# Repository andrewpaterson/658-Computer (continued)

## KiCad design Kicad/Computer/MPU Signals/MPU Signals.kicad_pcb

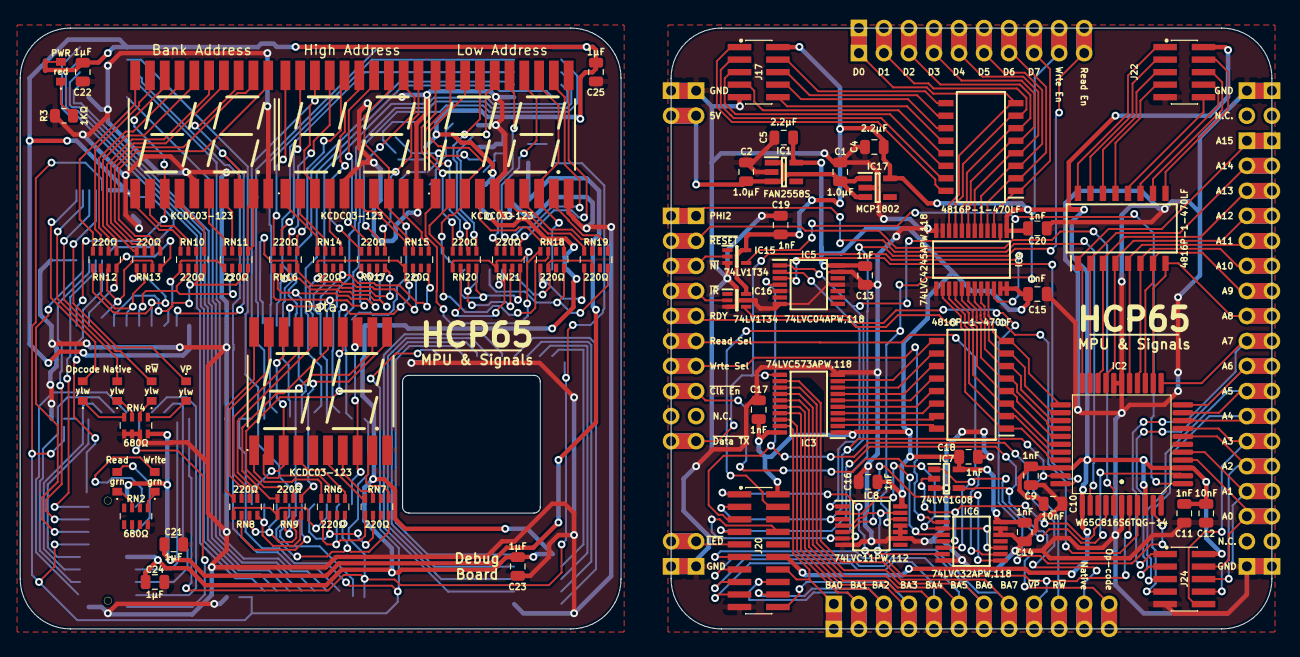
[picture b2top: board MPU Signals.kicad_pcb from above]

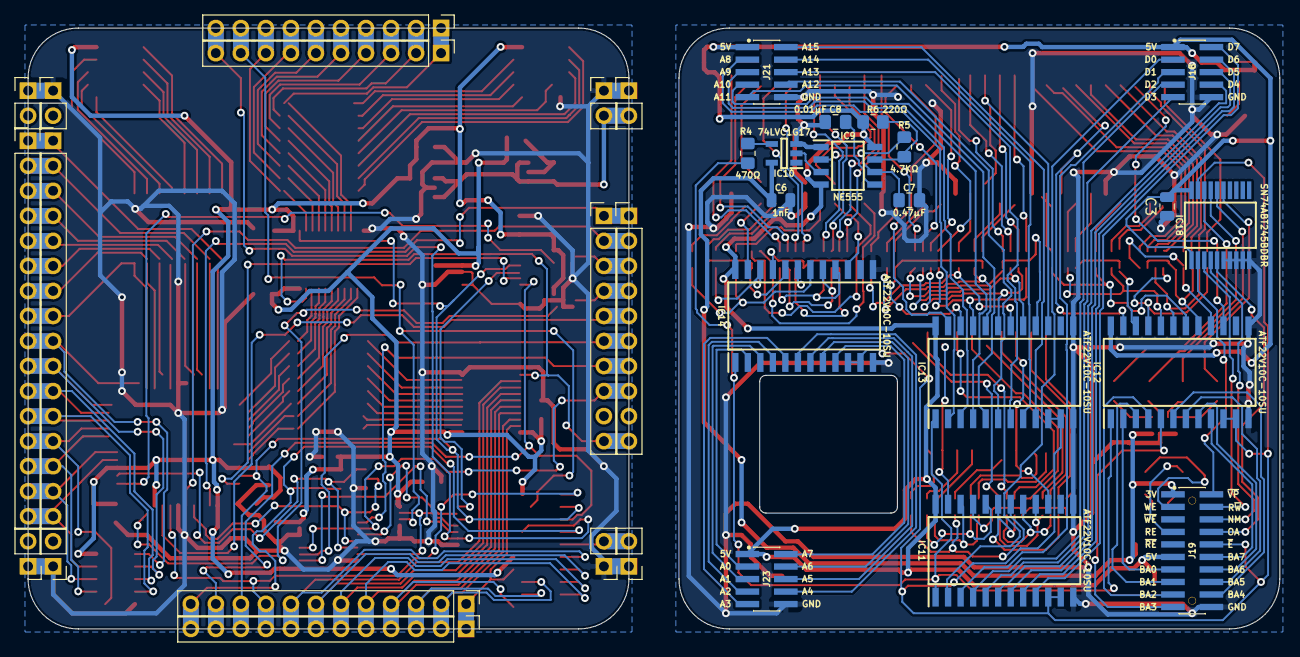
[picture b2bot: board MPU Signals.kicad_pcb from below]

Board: 2 copper layers, 127.0 x 61.0 mm, 104 parts (34 on the bottom side), 245 nets.

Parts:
C1, C2, C4, C5, C6, C9, C10, C11, C12, C13, C14, C15, C16, C17, C18, C19, C20, C21, C22, C23, C24, C25: C_0805
C3: C_Small; C_0805_2012Metric
C7, C8: C_Small; C_0805_2012Metric_Pad1.18x1.45mm_HandSolder
DS1, DS2, DS3, DS4: KCDC03-123; KCDC03123
IC1: FAN2558S38X; SOT95P270X145-5N
IC2: W65C816S6TQG-14; W65C816 PLCC 0.8mm 44 Pin
IC3: 74LVC573APW,118; SOP65P640X110-20N
IC4: 74LVC4245APW,118; SOP65P640X110-24N
IC5: 74LVC04APW,118; SOP65P640X110-14N
IC6: 74LVC32APW,118; SOP65P640X110-14N
IC7: 74LVC1G08GV,125; SOT95P275X110-5N
IC8: 74LVC11PW,112; SOP65P640X110-14N
IC9: NE555DRG4; SOIC127P600X175-8N
IC10: 74LVC1G17GV,125; SOT95P275X110-5N
IC11, IC12, IC13, IC14: ATF22V10C-10SU; SOIC127P1032X265-24N
IC15, IC16: 74LV1T34GWH; SOT65P212X110-5N
IC17: MCP1802T-5002I_OT; SOT95P270X145-5N
IC18: SN74ABT245BDBR; SOP65P780X200-20N
J1, J2, J3, J5, J6, J8, J9, J10: Conn_01x02_Male; PinHeader_1x02_P2.54mm_Vertical
J4, J11, J13, J14: Conn_01x10_Male; PinHeader_1x10_P2.54mm_Vertical
J7, J12: Conn_01x16_Male; PinHeader_1x16_P2.54mm_Vertical
J15: Conn_01x16_Male; PinHeader_1x12_P2.54mm_Vertical
J16: Conn_01x12_Male; PinHeader_1x12_P2.54mm_Vertical
J17, J22, J24: Conn_02x05_Counter_Clockwise; Pin_Socket_1.27mm 2x05
J18: Conn_02x05_Counter_Clockwise; Pin_Header_1.27mm 2x05
J19: SamacSys_Parts:Pin_Header_1.27mm 2x05; Pin_Header_1.27mm 2x10
J20: Conn_02x05_Counter_Clockwise; Pin_Socket_1.27mm 2x10
J21, J23: SamacSys_Parts:Pin_Header_1.27mm 2x05; Pin_Header_1.27mm 2x05
LED1: 150224SS73100; 150224SS73100A
LED2, LED5: 150224VS73100A
LED3, LED7, LED8, LED9: 150224YS73100A; 150224BS73100A
NT1: NetTie_2; NetTie-2_SMD_Pad0.5mm
R3: R_0805
R4, R5, R6: R_Small; R_0805_2012Metric_Pad1.20x1.40mm_HandSolder
RN1, RN3, RN5: 4816P-1-470LF; SOIC127P762X240-16N
RN2, RN4: CAY16-681J4LF; CAY16-J4
RN6, RN7, RN8, RN9, RN10, RN11, RN12, RN13, RN14, RN15, RN16, RN17, RN18, RN19, RN20, RN21: CAY16-221J4LF; CAY1647R0F4LF

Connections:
/3.8V: C5.1, C13.1, C14.1, C15.1, C16.1, C17.1, C18.1, IC1.5 (VOUT), IC3.1 (~OE), IC3.20 (3V), IC4.23 (3V), IC4.24 (3V), IC5.14 (3V), IC6.14 (3V), IC7.5 (3V), IC8.14 (3V), J20.20
/3.8V_{TOP}: C6.1, C21.1, IC10.5 (3V), J19.1, RN4.4 (R4)
/5V: C4.1, C9.1, C10.1, C11.1, C12.1, C19.1, C20.1, IC2.4 (~ABORT), IC2.9 (VCC), IC2.37 (VCC), IC2.40 (BE), IC4.1 (5V), IC15.5 (5V), IC16.5 (5V), IC17.5 (VOUT), J17.10, J20.15, J22.10, J24.10
/5V_{TOP}: C3.2, C22.1, C23.1, C24.1, C25.1, IC9.4 (RESET), IC9.8 (VCC), IC11.24 (5V), IC12.24 (5V), IC13.24 (5V), IC14.24 (5V), IC18.1 (DIR), IC18.20 (5V), J18.1, J19.6, J21.1, J23.1, NT1.1, R6.2
/A0: IC2.10 (A0), J7.16, J12.16, J24.9
/A0_{TOP}: IC14.2 (IN0), J23.2
/A1: IC2.11 (A1), J7.15, J12.15, J24.8
/A1_{TOP}: IC14.3 (IN1), J23.3
/A2: IC2.13 (A2), J7.14, J12.14, J24.7
/A2_{TOP}: IC14.4 (IN2/PD), J23.4
/A3: IC2.14 (A3), J7.13, J12.13, J24.6
/A3_{TOP}: IC14.5 (IN3), J23.5
/A4: IC2.15 (A4), J7.12, J12.12, J24.4
/A4_{TOP}: IC14.6 (IN4), J23.7
/A5: IC2.16 (A5), J7.11, J12.11, J24.3
/A5_{TOP}: IC14.7 (IN5), J23.8
/A6: IC2.17 (A6), J7.10, J12.10, J24.2
/A6_{TOP}: IC14.8 (IN6), J23.9
/A7: IC2.18 (A7), J7.9, J12.9, J24.1
/A7_{TOP}: IC14.9 (IN7), J23.10
/A8: IC2.19 (A8), J7.8, J12.8, RN3.8
/A9: IC2.20 (A9), J7.7, J12.7, RN3.7
/A10: IC2.21 (A10), J7.6, J12.6, RN3.6
/A11: IC2.22 (A11), J7.5, J12.5, RN3.5
/A12: IC2.25 (A12), J7.4, J12.4, RN3.4
/A13: IC2.26 (A13), J7.3, J12.3, RN3.3
/A14: IC2.27 (A14), J7.2, J12.2, RN3.2
/A15: IC2.28 (A15), J7.1, J12.1, RN3.1
/BA0: IC3.19 (Q0), J15.1, J16.1, J20.14
/BA0_{TOP}: IC12.2 (IN0), J19.7
/BA1: IC3.18 (Q1), J15.2, J16.2, J20.13
/BA1_{TOP}: IC12.3 (IN1), J19.8
/BA2: IC3.17 (Q2), J15.3, J16.3, J20.12
/BA2_{TOP}: IC12.4 (IN2/PD), J19.9
/BA3: IC3.16 (Q3), J15.4, J16.4, J20.11
/BA3_{TOP}: IC12.5 (IN3), J19.10
/BA4: IC3.15 (Q4), J15.5, J16.5, J20.9
/BA4_{TOP}: IC12.6 (IN4), J19.12
/BA5: IC3.14 (Q5), J15.6, J16.6, J20.8
/BA5_{TOP}: IC12.7 (IN5), J19.13
/BA6: IC3.13 (Q6), J15.7, J16.7, J20.7
/BA6_{TOP}: IC12.8 (IN6), J19.14
/BA7: IC3.12 (Q7), J15.8, J16.8, J20.6
/BA7_{TOP}: IC12.9 (IN7), J19.15
/BA/D0: IC2.36 (D0), IC4.14 (B7), RN1.1
/BA/D1: IC2.35 (D1), IC4.15 (B6), RN1.2
/BA/D2: IC2.34 (D2), IC4.16 (B5), RN1.3
/BA/D3: IC2.33 (D3), IC4.17 (B4), RN1.4
/BA/D4: IC2.32 (D4), IC4.18 (B3), RN1.5
/BA/D5: IC2.31 (D5), IC4.19 (B2), RN1.6
/BA/D6: IC2.30 (D6), IC4.20 (B1), RN1.7
/BA/D7: IC2.29 (D7), IC4.21 (B0), RN1.8
/Bank Address Display/Digit 0 A Seg: IC12.17 (I/O3), RN12.7 (R2), RN13.7 (R2)
/Bank Address Display/Digit 0 B Seg: IC12.16 (I/O2), RN12.8 (R1), RN13.8 (R1)
/Bank Address Display/Digit 0 C Seg: IC12.18 (I/O4), RN10.4 (R4), RN11.4 (R4)
/Bank Address Display/Digit 0 D Seg: IC12.20 (I/O6), RN10.2 (R2), RN11.2 (R2)
/Bank Address Display/Digit 0 E Seg: IC12.22 (I/O8), RN10.1 (R1), RN11.1 (R1)
/Bank Address Display/Digit 0 F Seg: IC12.19 (I/O5), RN12.6 (R3), RN13.6 (R3)
/Bank Address Display/Digit 0 G Seg: IC12.21 (I/O7), RN12.5 (R4), RN13.5 (R4)
/Bank Address Display/Digit L0 Cathode: DS2.3 (Cathode_{(Left)}), DS2.18 (Cathode_{(Left)}), IC12.15 (I/O1)
/Bank Address Display/Digit R0 Cathode: DS2.8 (Cathode_{(Right)}), DS2.13 (Cathode_{(Right)}), IC12.23 (I/O9)
/Clock: IC11.1 (CLK/IN), IC12.1 (CLK/IN), IC13.1 (CLK/IN), IC14.1 (CLK/IN), R4.1
/D0: IC4.10 (A7), J13.1, J14.1, RN5.8
/D1: IC4.9 (A6), J13.2, J14.2, RN5.7
/D2: IC4.8 (A5), J13.3, J14.3, RN5.6
/D3: IC4.7 (A4), J13.4, J14.4, RN5.5
/D4: IC4.6 (A3), J13.5, J14.5, RN5.4
/D5: IC4.5 (A2), J13.6, J14.6, RN5.3
/D6: IC4.4 (A1), J13.7, J14.7, RN5.2
/D7: IC4.3 (A0), J13.8, J14.8, RN5.1
/Data Display/Digit 0 A Seg: IC11.17 (I/O3), RN8.7 (R2), RN9.7 (R2)
/Data Display/Digit 0 B Seg: IC11.16 (I/O2), RN8.8 (R1), RN9.8 (R1)
/Data Display/Digit 0 C Seg: IC11.18 (I/O4), RN6.4 (R4), RN7.4 (R4)
/Data Display/Digit 0 D Seg: IC11.20 (I/O6), RN6.2 (R2), RN7.2 (R2)
/Data Display/Digit 0 E Seg: IC11.22 (I/O8), RN6.1 (R1), RN7.1 (R1)
/Data Display/Digit 0 F Seg: IC11.19 (I/O5), RN8.6 (R3), RN9.6 (R3)
/Data Display/Digit 0 G Seg: IC11.21 (I/O7), RN8.5 (R4), RN9.5 (R4)
/Data Display/Digit L0 Cathode: DS1.3 (Cathode_{(Left)}), DS1.18 (Cathode_{(Left)}), IC11.15 (I/O1)
/Data Display/Digit R0 Cathode: DS1.8 (Cathode_{(Right)}), DS1.13 (Cathode_{(Right)}), IC11.23 (I/O9)
/E: IC2.39 (E), IC5.3 (2A)
/GND: C1.2, C2.2, C4.2, C5.2, C9.2, C10.2, C11.2, C12.2, C13.2, C14.2, C15.2, C16.2, C17.2, C18.2, C19.2, C20.2, IC1.2 (GND), IC2.1 (GND), IC2.23 (GND), IC2.24 (GND), IC3.10 (GND), IC4.11 (GND), IC4.12 (GND), IC4.13 (GND), IC5.5 (3A), IC5.7 (GND), IC5.9 (4A), IC5.11 (5A), IC5.13 (6A), IC6.7 (GND), IC6.12 (4A), IC6.13 (4B), IC7.3 (GND), IC8.7 (GND), IC8.9 (3A), IC8.10 (3B), IC8.11 (3C), IC15.3 (GND), IC16.3 (GND), IC17.2 (VSS), J1.1, J2.1, J3.1, J5.1, J6.1, J8.1, J9.1, J10.1, J17.5, J20.10, J22.5, J24.5
/GND_{TOP}: C3.1, C6.2, C7.2, C8.2, C21.2, C22.2, C23.2, C24.2, C25.2, DS1.5 (Dot_{(Left)}), DS1.10 (Dot_{(Right)}), DS2.5 (Dot_{(Left)}), DS2.10 (Dot_{(Right)}), DS3.5 (Dot_{(Left)}), DS3.10 (Dot_{(Right)}), DS4.5 (Dot_{(Left)}), DS4.10 (Dot_{(Right)}), IC9.1 (GND), IC10.3 (GND), IC11.12 (GND), IC11.13 (IN10), IC12.12 (GND), IC12.13 (IN10), IC13.12 (GND), IC13.13 (IN10), IC14.12 (GND), IC14.13 (IN10), IC18.6 (A5), IC18.7 (A6), IC18.8 (A7), IC18.9 (A8), IC18.10 (GND), J18.6, J19.11, J21.6, J23.6, R3.2, RN2.2 (R2), RN2.4 (R4), RN4.1 (R1), RN4.2 (R2), RN4.3 (R3)
/High Address Display/Digit 0 A Seg: IC13.17 (I/O3), RN16.7 (R2), RN17.7 (R2)
/High Address Display/Digit 0 B Seg: IC13.16 (I/O2), RN16.8 (R1), RN17.8 (R1)
/High Address Display/Digit 0 C Seg: IC13.18 (I/O4), RN14.4 (R4), RN15.4 (R4)
/High Address Display/Digit 0 D Seg: IC13.20 (I/O6), RN14.2 (R2), RN15.2 (R2)
/High Address Display/Digit 0 E Seg: IC13.22 (I/O8), RN14.1 (R1), RN15.1 (R1)
/High Address Display/Digit 0 F Seg: IC13.19 (I/O5), RN16.6 (R3), RN17.6 (R3)
/High Address Display/Digit 0 G Seg: IC13.21 (I/O7), RN16.5 (R4), RN17.5 (R4)
/High Address Display/Digit L0 Cathode: DS3.3 (Cathode_{(Left)}), DS3.18 (Cathode_{(Left)}), IC13.15 (I/O1)
/High Address Display/Digit R0 Cathode: DS3.8 (Cathode_{(Right)}), DS3.13 (Cathode_{(Right)}), IC13.23 (I/O9)
/LA8: J22.9, RN3.9
/LA8_{TOP}: IC13.2 (IN0), J21.2
/LA9: J22.8, RN3.10
/LA9_{TOP}: IC13.3 (IN1), J21.3
/LA10: J22.7, RN3.11
/LA10_{TOP}: IC13.4 (IN2/PD), J21.4
/LA11: J22.6, RN3.12
/LA11_{TOP}: IC13.5 (IN3), J21.5
/LA12: J22.4, RN3.13
/LA12_{TOP}: IC13.6 (IN4), J21.7
/LA13: J22.3, RN3.14
/LA13_{TOP}: IC13.7 (IN5), J21.8
/LA14: J22.2, RN3.15
/LA14_{TOP}: IC13.8 (IN6), J21.9
/LA15: J22.1, RN3.16
/LA15_{TOP}: IC13.9 (IN7), J21.10
/LD0: J17.9, RN5.9
/LD0_{TOP}: IC11.2 (IN0), J18.2
/LD1: J17.8, RN5.10
/LD1_{TOP}: IC11.3 (IN1), J18.3
/LD2: J17.7, RN5.11
/LD2_{TOP}: IC11.4 (IN2/PD), J18.4
/LD3: J17.6, RN5.12
/LD3_{TOP}: IC11.5 (IN3), J18.5
/LD4: J17.4, RN5.13
/LD4_{TOP}: IC11.6 (IN4), J18.7
/LD5: J17.3, RN5.14
/LD5_{TOP}: IC11.7 (IN5), J18.8
/LD6: J17.2, RN5.15
/LD6_{TOP}: IC11.8 (IN6), J18.9
/LD7: J17.1, RN5.16
/LD7_{TOP}: IC11.9 (IN7), J18.10
/Low Address Display/Digit 0 A Seg: IC14.17 (I/O3), RN20.7 (R2), RN21.7 (R2)
/Low Address Display/Digit 0 B Seg: IC14.16 (I/O2), RN20.8 (R1), RN21.8 (R1)
/Low Address Display/Digit 0 C Seg: IC14.18 (I/O4), RN18.4 (R4), RN19.4 (R4)
/Low Address Display/Digit 0 D Seg: IC14.20 (I/O6), RN18.2 (R2), RN19.2 (R2)
/Low Address Display/Digit 0 E Seg: IC14.22 (I/O8), RN18.1 (R1), RN19.1 (R1)
/Low Address Display/Digit 0 F Seg: IC14.19 (I/O5), RN20.6 (R3), RN21.6 (R3)
/Low Address Display/Digit 0 G Seg: IC14.21 (I/O7), RN20.5 (R4), RN21.5 (R4)
/Low Address Display/Digit L0 Cathode: DS4.3 (Cathode_{(Left)}), DS4.18 (Cathode_{(Left)}), IC14.15 (I/O1)
/Low Address Display/Digit R0 Cathode: DS4.8 (Cathode_{(Right)}), DS4.13 (Cathode_{(Right)}), IC14.23 (I/O9)
/Native Mode: IC5.4 (2Y), J15.11, J16.11, J20.3
/Native Mode_{TOP}: IC18.4 (A3), J19.18
/Opcode Address: IC7.4 (Y), J15.12, J16.12, J20.4
/Opcode Address_{TOP}: IC18.5 (A4), J19.17
/PHI2: IC2.41 (PHI2), J4.1, J11.1
/Power LED: LED1.2, NT1.2
/RDY: IC2.3 (RDY), J4.5, J11.5
/Read Enable: IC8.6 (2Y), J13.10, J14.10, J20.17
/Read Enable_{TOP}: J19.4, LED5.2
/Read Selector: IC6.9 (3A), J4.6, J11.6
/Read Selector OR ~Clock Enable: IC6.8 (3Y), IC8.5 (2C)
/R~W: IC2.38 (R~W), IC4.2 (DIR), IC5.1 (1A), IC8.3 (2A), J15.10, J16.10, J20.2
/R~W_{TOP}: IC18.3 (A2), J19.19
/Source 5V: C1.1, C2.1, IC1.1 (VIN), IC1.3 (EN), IC17.1 (VIN), IC17.3 (~SHDN), J1.2, J3.2
/VDA: IC2.43 (VDA), IC6.4 (2A), IC7.2 (A)
/VPA: IC2.8 (VPA), IC6.5 (2B), IC7.1 (B)
/Valid Address: IC6.6 (2Y), IC8.4 (2B), IC8.13 (1C)
/Write Enable: IC8.12 (1Y), J13.9, J14.9, J20.19
/Write Enable_{TOP}: J19.2, LED2.2
/Write Selector: IC6.1 (1A), J4.7, J11.7
/Write Selector OR ~Clock Enable: IC6.3 (1Y), IC8.2 (1B)
/~Clock Enable: IC6.2 (1B), IC6.10 (3B), J4.8, J11.8
/~Data Transmit: IC3.11 (LE), IC4.22 (~OE), J4.10, J11.10
/~IRQ: IC16.2 (A), J4.4, J11.4
/~IRQ^{5V}: IC2.5 (~IRQ), IC16.4 (Y)
/~LED Enable: J2.2, J5.2, J20.5
/~LED Enable_{TOP}: IC11.10 (IN8), IC11.11 (IN9), IC12.10 (IN8), IC12.11 (IN9), IC13.10 (IN8), IC13.11 (IN9), IC14.10 (IN8), IC14.11 (IN9), IC18.19 (~OE), J19.16
/~NMI: IC15.2 (A), J4.3, J11.3
/~NMI^{5V}: IC2.7 (~NMI), IC15.4 (Y)
/~Reset: IC2.44 (~RES), J4.2, J11.2
/~RW: IC5.2 (1Y), IC8.1 (1A)
/~VP: IC2.2 (~VP), J15.9, J16.9, J20.1
/~VP_{TOP}: IC18.2 (A1), J19.20
unnamed: C7.1, IC9.2 (TRIG), IC9.6 (THRES), R5.1
unnamed: C8.1, IC9.5 (CONT)
unnamed: DS1.1 (E-Seg_{(Left)}), RN6.8 (R1)
unnamed: DS1.2 (D-Seg_{(Left)}), RN6.7 (R2)
unnamed: DS1.4 (C-Seg_{(Left)}), RN6.5 (R4)
unnamed: DS1.6 (E-Seg_{(Right)}), RN7.8 (R1)
unnamed: DS1.7 (D-Seg_{(Right)}), RN7.7 (R2)
unnamed: DS1.9 (C-Seg_{(Right)}), RN7.5 (R4)
unnamed: DS1.11 (B-Seg_{(Right)}), RN9.1 (R1)
unnamed: DS1.12 (A-Seg_{(Right)}), RN9.2 (R2)
unnamed: DS1.14 (F-Seg_{(Right)}), RN9.3 (R3)
unnamed: DS1.15 (G-Seg_{(Right)}), RN9.4 (R4)
unnamed: DS1.16 (B-Seg_{(Left)}), RN8.1 (R1)
unnamed: DS1.17 (A-Seg_{(Left)}), RN8.2 (R2)
unnamed: DS1.19 (F-Seg_{(Left)}), RN8.3 (R3)
unnamed: DS1.20 (G-Seg_{(Left)}), RN8.4 (R4)
unnamed: DS2.1 (E-Seg_{(Left)}), RN10.8 (R1)
unnamed: DS2.2 (D-Seg_{(Left)}), RN10.7 (R2)
unnamed: DS2.4 (C-Seg_{(Left)}), RN10.5 (R4)
unnamed: DS2.6 (E-Seg_{(Right)}), RN11.8 (R1)
unnamed: DS2.7 (D-Seg_{(Right)}), RN11.7 (R2)
unnamed: DS2.9 (C-Seg_{(Right)}), RN11.5 (R4)
unnamed: DS2.11 (B-Seg_{(Right)}), RN13.1 (R1)
unnamed: DS2.12 (A-Seg_{(Right)}), RN13.2 (R2)
unnamed: DS2.14 (F-Seg_{(Right)}), RN13.3 (R3)
unnamed: DS2.15 (G-Seg_{(Right)}), RN13.4 (R4)
unnamed: DS2.16 (B-Seg_{(Left)}), RN12.1 (R1)
unnamed: DS2.17 (A-Seg_{(Left)}), RN12.2 (R2)
unnamed: DS2.19 (F-Seg_{(Left)}), RN12.3 (R3)
unnamed: DS2.20 (G-Seg_{(Left)}), RN12.4 (R4)
unnamed: DS3.1 (E-Seg_{(Left)}), RN14.8 (R1)
unnamed: DS3.2 (D-Seg_{(Left)}), RN14.7 (R2)
unnamed: DS3.4 (C-Seg_{(Left)}), RN14.5 (R4)
unnamed: DS3.6 (E-Seg_{(Right)}), RN15.8 (R1)
unnamed: DS3.7 (D-Seg_{(Right)}), RN15.7 (R2)
unnamed: DS3.9 (C-Seg_{(Right)}), RN15.5 (R4)
unnamed: DS3.11 (B-Seg_{(Right)}), RN17.1 (R1)
unnamed: DS3.12 (A-Seg_{(Right)}), RN17.2 (R2)
unnamed: DS3.14 (F-Seg_{(Right)}), RN17.3 (R3)
unnamed: DS3.15 (G-Seg_{(Right)}), RN17.4 (R4)
unnamed: DS3.16 (B-Seg_{(Left)}), RN16.1 (R1)
unnamed: DS3.17 (A-Seg_{(Left)}), RN16.2 (R2)
unnamed: DS3.19 (F-Seg_{(Left)}), RN16.3 (R3)
unnamed: DS3.20 (G-Seg_{(Left)}), RN16.4 (R4)
unnamed: DS4.1 (E-Seg_{(Left)}), RN18.8 (R1)
unnamed: DS4.2 (D-Seg_{(Left)}), RN18.7 (R2)
unnamed: DS4.4 (C-Seg_{(Left)}), RN18.5 (R4)
unnamed: DS4.6 (E-Seg_{(Right)}), RN19.8 (R1)
unnamed: DS4.7 (D-Seg_{(Right)}), RN19.7 (R2)
unnamed: DS4.9 (C-Seg_{(Right)}), RN19.5 (R4)
unnamed: DS4.11 (B-Seg_{(Right)}), RN21.1 (R1)
unnamed: DS4.12 (A-Seg_{(Right)}), RN21.2 (R2)
unnamed: DS4.14 (F-Seg_{(Right)}), RN21.3 (R3)
unnamed: DS4.15 (G-Seg_{(Right)}), RN21.4 (R4)
unnamed: DS4.16 (B-Seg_{(Left)}), RN20.1 (R1)
unnamed: DS4.17 (A-Seg_{(Left)}), RN20.2 (R2)
unnamed: DS4.19 (F-Seg_{(Left)}), RN20.3 (R3)
unnamed: DS4.20 (G-Seg_{(Left)}), RN20.4 (R4)
unnamed: IC3.2 (D0), RN1.16
unnamed: IC3.3 (D1), RN1.15
unnamed: IC3.4 (D2), RN1.14
unnamed: IC3.5 (D3), RN1.13
unnamed: IC3.6 (D4), RN1.12
unnamed: IC3.7 (D5), RN1.11
unnamed: IC3.8 (D6), RN1.10
unnamed: IC3.9 (D7), RN1.9
unnamed: IC9.7 (DISCH), R5.2, R6.1
unnamed: IC9.3 (OUT), IC10.2 (A)
unnamed: IC10.4 (Y), R4.2
unnamed: IC18.15 (B4), LED9.2
unnamed: IC18.16 (B3), LED8.2
unnamed: IC18.17 (B2), LED7.2
unnamed: IC18.18 (B1), LED3.1
unnamed: LED1.1, R3.1
unnamed: LED2.1, RN2.5 (R4)
unnamed: LED3.2, RN4.5 (R4)
unnamed: LED5.1, RN2.7 (R2)
unnamed: LED7.1, RN4.6 (R3)
unnamed: LED8.1, RN4.7 (R2)
unnamed: LED9.1, RN4.8 (R1)

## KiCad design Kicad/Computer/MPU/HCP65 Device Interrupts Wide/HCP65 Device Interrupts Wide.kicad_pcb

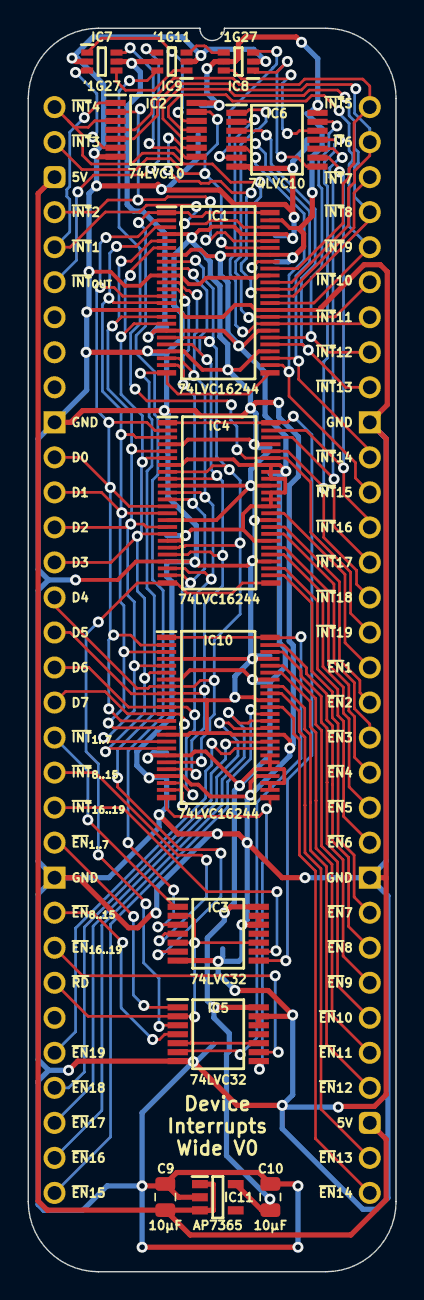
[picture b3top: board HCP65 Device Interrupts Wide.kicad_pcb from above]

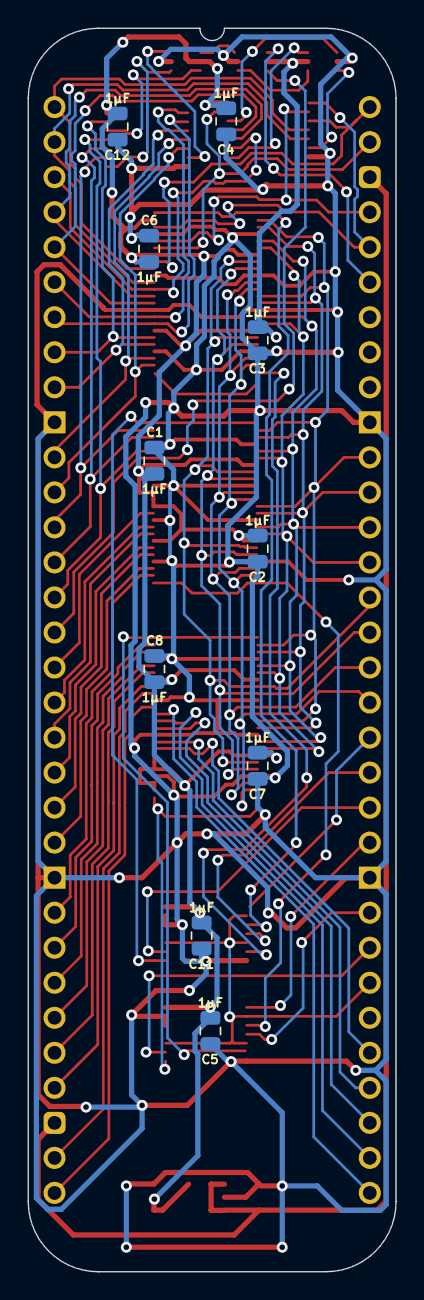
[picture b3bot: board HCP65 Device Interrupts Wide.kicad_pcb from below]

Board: 2 copper layers, 26.7 x 90.2 mm, 26 parts (12 on the bottom side), 71 nets.

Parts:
C1, C2, C3, C4, C5, C6, C7, C8, C11, C12: 1μF; C_0805
C9, C10: 10μF; C_0805
IC1, IC4, IC10: 74LVC16244ADGG,112; 74LVC16244ADGG112
IC2, IC6: SN74LVC10APWR; SOP65P640X120-14N
IC3, IC5: 74LVC32APW,118; SOP65P640X110-14N
IC7, IC8: 74LVC1G27GW,125; SOP65P210X110-6N
IC9: 74LVC1G11GW-Q100H; SOP65P210X110-6N
IC11: AP7365-33WG-7; SOT95P285X130-5N
J1, J3: Pin_Header_01x32; PinHeader_1x32_P2.54mm_Vertical
J2: Conn_02x32_Counter_Clockwise; DIP-64_Board_W22.86mm

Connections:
5V: C9.1, IC11.1 (6VIn), IC11.3 (EN), J2.3, J2.35
/3.3V: C1.1, C2.1, C3.1, C4.1, C5.1, C6.1, C7.1, C8.1, C10.1, C11.1, C12.1, IC1.7 (3V), IC1.18 (3V), IC1.31 (3V), IC1.42 (3V), IC1.47 (1A0), IC2.14 (3V), IC3.14 (3V), IC4.7 (3V), IC4.18 (3V), IC4.31 (3V), IC4.36 (3A0), IC4.37 (2A3), IC4.38 (2A2), IC4.40 (2A1), IC4.41 (2A0), IC4.42 (3V), IC5.14 (3V), IC6.14 (3V), IC7.5 (3V), IC8.5 (3V), IC9.5 (3V), IC10.7 (3V), IC10.18 (3V), IC10.26 (4A3), IC10.27 (4A2), IC10.29 (4A1), IC10.30 (4A0), IC10.31 (3V), IC10.42 (3V), IC11.5 (3.3VOut)
/~Read Device Enable_{ 1..7}: IC4.24 (4~OE), IC4.25 (3~OE), IC5.3 (1Y)
/~Read Device Enable_{ 8..15}: IC5.6 (2Y), IC10.1 (1~OE), IC10.48 (2~OE)
/~Read Device Enable_{ 16..19}: IC5.8 (3Y), IC10.24 (4~OE), IC10.25 (3~OE)
/~Read Device Interrupt_{ 1..7}: IC1.1 (1~OE), IC1.48 (2~OE), IC3.3 (1Y)
/~Read Device Interrupt_{ 8..15}: IC1.24 (4~OE), IC1.25 (3~OE), IC3.6 (2Y)
/~Read Device Interrupt_{ 16..19}: IC3.8 (3Y), IC4.1 (1~OE), IC4.48 (2~OE)
D0: IC1.2 (1Y0), IC1.13 (3Y0), IC4.2 (1Y0), IC4.13 (3Y0), IC10.2 (1Y0), IC10.13 (3Y0), J2.11
D1: IC1.3 (1Y1), IC1.14 (3Y1), IC4.3 (1Y1), IC4.14 (3Y1), IC10.3 (1Y1), IC10.14 (3Y1), J2.12
D2: IC1.5 (1Y2), IC1.16 (3Y2), IC4.5 (1Y2), IC4.16 (3Y2), IC10.5 (1Y2), IC10.16 (3Y2), J2.13
D3: IC1.6 (1Y3), IC1.17 (3Y3), IC4.6 (1Y3), IC4.17 (3Y3), IC10.6 (1Y3), IC10.17 (3Y3), J2.14
D4: IC1.8 (2Y0), IC1.19 (4Y0), IC4.8 (2Y0), IC4.19 (4Y0), IC10.8 (2Y0), IC10.19 (4Y0), J2.15
D5: IC1.9 (2Y1), IC1.20 (4Y1), IC4.9 (2Y1), IC4.20 (4Y1), IC10.9 (2Y1), IC10.20 (4Y1), J2.16
D6: IC1.11 (2Y2), IC1.22 (4Y2), IC4.11 (2Y2), IC4.22 (4Y2), IC10.11 (2Y2), IC10.22 (4Y2), J2.17
D7: IC1.12 (2Y3), IC1.23 (4Y3), IC4.12 (2Y3), IC4.23 (4Y3), IC10.12 (2Y3), IC10.23 (4Y3), J2.18
GND: C1.2, C2.2, C3.2, C4.2, C5.2, C6.2, C7.2, C8.2, C9.2, C10.2, C11.2, C12.2, IC1.4 (GND), IC1.10 (GND), IC1.15 (GND), IC1.21 (GND), IC1.28 (GND), IC1.34 (GND), IC1.39 (GND), IC1.45 (GND), IC2.7 (GND), IC3.7 (GND), IC3.12 (4A), IC3.13 (4B), IC4.4 (GND), IC4.10 (GND), IC4.15 (GND), IC4.21 (GND), IC4.28 (GND), IC4.34 (GND), IC4.39 (GND), IC4.45 (GND), IC5.7 (GND), IC5.12 (4A), IC5.13 (4B), IC6.7 (GND), IC7.2 (GND), IC8.2 (GND), IC9.2 (GND), IC10.4 (GND), IC10.10 (GND), IC10.15 (GND), IC10.21 (GND), IC10.28 (GND), IC10.34 (GND), IC10.39 (GND), IC10.45 (GND), IC11.2 (GND), J2.10, J2.23, J2.42, J2.55
unnamed: IC2.12 (1Y), IC7.1 (A)
unnamed: IC2.6 (2Y), IC7.3 (B)
unnamed: IC2.8 (3Y), IC7.6 (C)
unnamed: IC6.12 (1Y), IC8.6 (C)
unnamed: IC6.6 (2Y), IC8.3 (B)
unnamed: IC6.8 (3Y), IC8.1 (A)
unnamed: IC7.4 (Y), IC9.1 (A)
unnamed: IC8.4 (Y), IC9.3 (B)
~Device Enable_{ 1..7}: IC5.1 (1A), J2.22
~Device Enable_{ 8..15}: IC5.4 (2A), J2.24
~Device Enable_{ 16..19}: IC5.9 (3A), J2.25
~Device Interrupt_{ 1..7}: IC3.1 (1A), J2.19
~Device Interrupt_{ 8..15}: IC3.4 (2A), J2.20
~Device Interrupt_{ 16..19}: IC3.9 (3A), J2.21
~Enable_{Device}1: IC4.35 (3A1), J2.48
~Enable_{Device}2: IC4.33 (3A2), J2.47
~Enable_{Device}3: IC4.32 (3A3), J2.46
~Enable_{Device}4: IC4.30 (4A0), J2.45
~Enable_{Device}5: IC4.29 (4A1), J2.44
~Enable_{Device}6: IC4.27 (4A2), J2.43
~Enable_{Device}7: IC4.26 (4A3), J2.41
~Enable_{Device}8: IC10.47 (1A0), J2.40
~Enable_{Device}9: IC10.46 (1A1), J2.39
~Enable_{Device}10: IC10.44 (1A2), J2.38
~Enable_{Device}11: IC10.43 (1A3), J2.37
~Enable_{Device}12: IC10.41 (2A0), J2.36
~Enable_{Device}13: IC10.40 (2A1), J2.34
~Enable_{Device}14: IC10.38 (2A2), J2.33
~Enable_{Device}15: IC10.37 (2A3), J2.32
~Enable_{Device}16: IC10.36 (3A0), J2.31
~Enable_{Device}17: IC10.35 (3A1), J2.30
~Enable_{Device}18: IC10.33 (3A2), J2.29
~Enable_{Device}19: IC10.32 (3A3), J2.28
~INT: IC9.4 (Y), J2.6
~Interrupt_{Device}1: IC1.46 (1A1), IC2.1 (1A), J2.5
~Interrupt_{Device}2: IC1.44 (1A2), IC2.2 (1B), J2.4
~Interrupt_{Device}3: IC1.43 (1A3), IC2.13 (1C), J2.2
~Interrupt_{Device}4: IC1.41 (2A0), IC2.3 (2A), J2.1
~Interrupt_{Device}5: IC1.40 (2A1), IC2.4 (2B), J2.64
~Interrupt_{Device}6: IC1.38 (2A2), IC2.5 (2C), J2.63
~Interrupt_{Device}7: IC1.37 (2A3), IC2.9 (3A), J2.62
~Interrupt_{Device}8: IC1.36 (3A0), IC2.10 (3B), J2.61
~Interrupt_{Device}9: IC1.35 (3A1), IC2.11 (3C), J2.60
~Interrupt_{Device}10: IC1.33 (3A2), IC6.1 (1A), J2.59
~Interrupt_{Device}11: IC1.32 (3A3), IC6.2 (1B), J2.58
~Interrupt_{Device}12: IC1.30 (4A0), IC6.13 (1C), J2.57
~Interrupt_{Device}13: IC1.29 (4A1), IC6.3 (2A), J2.56
~Interrupt_{Device}14: IC1.27 (4A2), IC6.4 (2B), J2.54
~Interrupt_{Device}15: IC1.26 (4A3), IC6.5 (2C), J2.53
~Interrupt_{Device}16: IC4.47 (1A0), IC6.9 (3A), J2.52
~Interrupt_{Device}17: IC4.46 (1A1), IC6.10 (3B), J2.51
~Interrupt_{Device}18: IC4.44 (1A2), IC6.11 (3C), J2.50
~Interrupt_{Device}19: IC4.43 (1A3), IC9.6 (C), J2.49
~RD: IC3.2 (1B), IC3.5 (2B), IC3.10 (3B), IC5.2 (1B), IC5.5 (2B), IC5.10 (3B), J2.26

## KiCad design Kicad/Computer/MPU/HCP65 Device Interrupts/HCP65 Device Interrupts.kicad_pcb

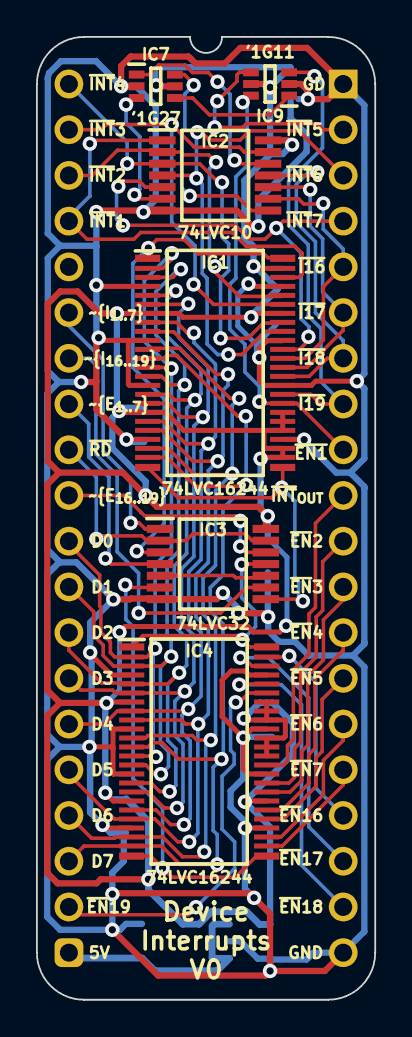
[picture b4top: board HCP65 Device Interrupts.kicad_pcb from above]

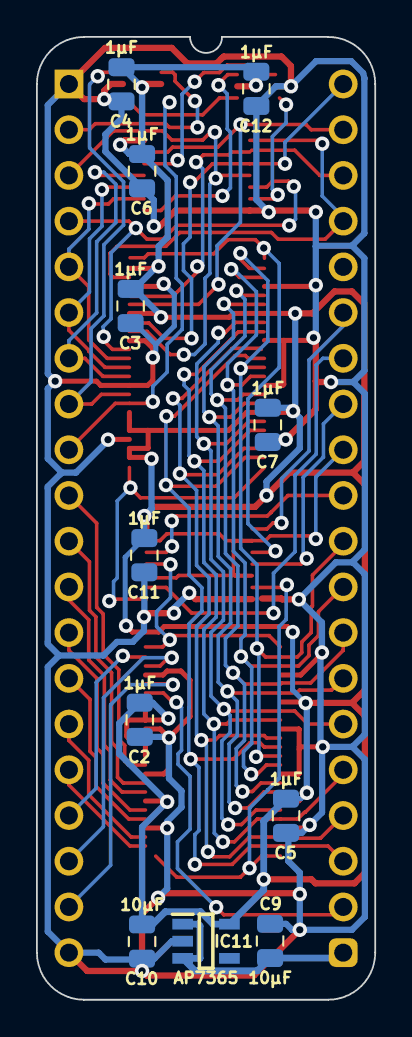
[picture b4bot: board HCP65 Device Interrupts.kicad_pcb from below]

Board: 2 copper layers, 18.8 x 53.5 mm, 20 parts (13 on the bottom side), 47 nets.

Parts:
C2, C3, C4, C5, C6, C7, C11, C12: 1μF; C_0805
C9, C10: 10μF; C_0805
IC1, IC4: 74LVC16244ADGG,112; 74LVC16244ADGG112
IC2: SN74LVC10APWR; SOP65P640X120-14N
IC3: 74LVC32APW,118; SOP65P640X110-14N
IC7: 74LVC1G27GW,125; SOP65P210X110-6N
IC9: 74LVC1G11GW-Q100H; SOP65P210X110-6N
IC11: AP7365-33WG-7; SOT95P285X130-5N
J1, J3: Pin_Header_01x20; PinHeader_1x20_P2.54mm_Vertical
J2: Conn_02x20_Counter_Clockwise; DIP-40_Board_W15.24mm_Alt

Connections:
5V: C9.1, IC11.1 (6VIn), IC11.3 (EN), J2.20
/3.3V: C2.1, C3.1, C4.1, C5.1, C6.1, C7.1, C10.1, C11.1, C12.1, IC1.7 (3V), IC1.18 (3V), IC1.26 (4A3), IC1.27 (4A2), IC1.29 (4A1), IC1.30 (4A0), IC1.31 (3V), IC1.42 (3V), IC1.47 (1A0), IC2.14 (3V), IC3.14 (3V), IC4.7 (3V), IC4.18 (3V), IC4.31 (3V), IC4.36 (3A0), IC4.37 (2A3), IC4.38 (2A2), IC4.40 (2A1), IC4.41 (2A0), IC4.42 (3V), IC7.5 (3V), IC9.5 (3V), IC11.5 (3.3VOut)
/~Read Device Enable_{ 1..7}: IC3.6 (2Y), IC4.24 (4~OE), IC4.25 (3~OE)
/~Read Device Enable_{ 16..19}: IC3.11 (4Y), IC4.1 (1~OE), IC4.48 (2~OE)
/~Read Device Interrupt_{ 1..7}: IC1.1 (1~OE), IC1.48 (2~OE), IC3.3 (1Y)
/~Read Device Interrupt_{ 16..19}: IC1.24 (4~OE), IC1.25 (3~OE), IC3.8 (3Y)
D0: IC1.2 (1Y0), IC1.13 (3Y0), IC4.2 (1Y0), IC4.13 (3Y0), J2.11
D1: IC1.3 (1Y1), IC1.14 (3Y1), IC4.3 (1Y1), IC4.14 (3Y1), J2.12
D2: IC1.5 (1Y2), IC1.16 (3Y2), IC4.5 (1Y2), IC4.16 (3Y2), J2.13
D3: IC1.6 (1Y3), IC1.17 (3Y3), IC4.6 (1Y3), IC4.17 (3Y3), J2.14
D4: IC1.8 (2Y0), IC1.19 (4Y0), IC4.8 (2Y0), IC4.19 (4Y0), J2.15
D5: IC1.9 (2Y1), IC1.20 (4Y1), IC4.9 (2Y1), IC4.20 (4Y1), J2.16
D6: IC1.11 (2Y2), IC1.22 (4Y2), IC4.11 (2Y2), IC4.22 (4Y2), J2.17
D7: IC1.12 (2Y3), IC1.23 (4Y3), IC4.12 (2Y3), IC4.23 (4Y3), J2.18
GND: C2.2, C3.2, C4.2, C5.2, C6.2, C7.2, C9.2, C10.2, C11.2, C12.2, IC1.4 (GND), IC1.10 (GND), IC1.15 (GND), IC1.21 (GND), IC1.28 (GND), IC1.34 (GND), IC1.39 (GND), IC1.45 (GND), IC2.7 (GND), IC3.7 (GND), IC4.4 (GND), IC4.10 (GND), IC4.15 (GND), IC4.21 (GND), IC4.28 (GND), IC4.34 (GND), IC4.39 (GND), IC4.45 (GND), IC7.2 (GND), IC9.2 (GND), IC11.2 (GND), J2.21, J2.40
unnamed: IC2.12 (1Y), IC7.1 (A)
unnamed: IC2.6 (2Y), IC7.3 (B)
unnamed: IC2.8 (3Y), IC7.6 (C)
unnamed: IC7.4 (Y), IC9.1 (A)
~Device Enable_{ 1..7}: IC3.4 (2A), J2.8
~Device Enable_{ 16..19}: IC3.12 (4A), J2.10
~Device Interrupt_{ 1..7}: IC3.1 (1A), J2.6
~Device Interrupt_{ 16..19}: IC3.9 (3A), J2.7
~Enable_{Device}1: IC4.35 (3A1), J2.31
~Enable_{Device}2: IC4.33 (3A2), J2.30
~Enable_{Device}3: IC4.32 (3A3), J2.29
~Enable_{Device}4: IC4.30 (4A0), J2.28
~Enable_{Device}5: IC4.29 (4A1), J2.27
~Enable_{Device}6: IC4.27 (4A2), J2.26
~Enable_{Device}7: IC4.26 (4A3), J2.25
~Enable_{Device}16: IC4.47 (1A0), J2.24
~Enable_{Device}17: IC4.46 (1A1), J2.23
~Enable_{Device}18: IC4.44 (1A2), J2.22
~Enable_{Device}19: IC4.43 (1A3), J2.19
~INT: IC9.4 (Y), J2.39
~Interrupt_{Device}1: IC1.46 (1A1), IC2.1 (1A), J2.4
~Interrupt_{Device}2: IC1.44 (1A2), IC2.2 (1B), J2.3
~Interrupt_{Device}3: IC1.43 (1A3), IC2.13 (1C), J2.2
~Interrupt_{Device}4: IC1.41 (2A0), IC2.3 (2A), J2.1
~Interrupt_{Device}5: IC1.40 (2A1), IC2.4 (2B), J2.38
~Interrupt_{Device}6: IC1.38 (2A2), IC2.5 (2C), J2.37
~Interrupt_{Device}7: IC1.37 (2A3), IC2.9 (3A), J2.36
~Interrupt_{Device}16: IC1.36 (3A0), IC2.10 (3B), J2.35
~Interrupt_{Device}17: IC1.35 (3A1), IC2.11 (3C), J2.34
~Interrupt_{Device}18: IC1.33 (3A2), IC9.3 (B), J2.33
~Interrupt_{Device}19: IC1.32 (3A3), IC9.6 (C), J2.32
~RD: IC3.2 (1B), IC3.5 (2B), IC3.10 (3B), IC3.13 (4B), J2.9

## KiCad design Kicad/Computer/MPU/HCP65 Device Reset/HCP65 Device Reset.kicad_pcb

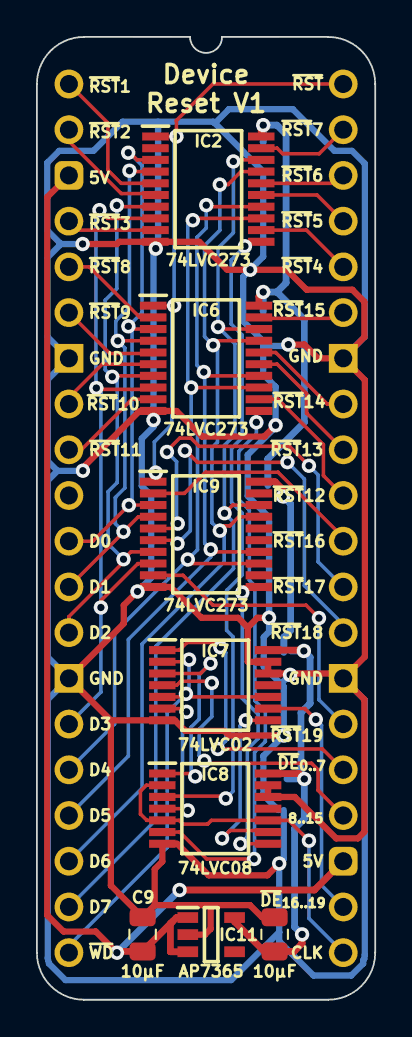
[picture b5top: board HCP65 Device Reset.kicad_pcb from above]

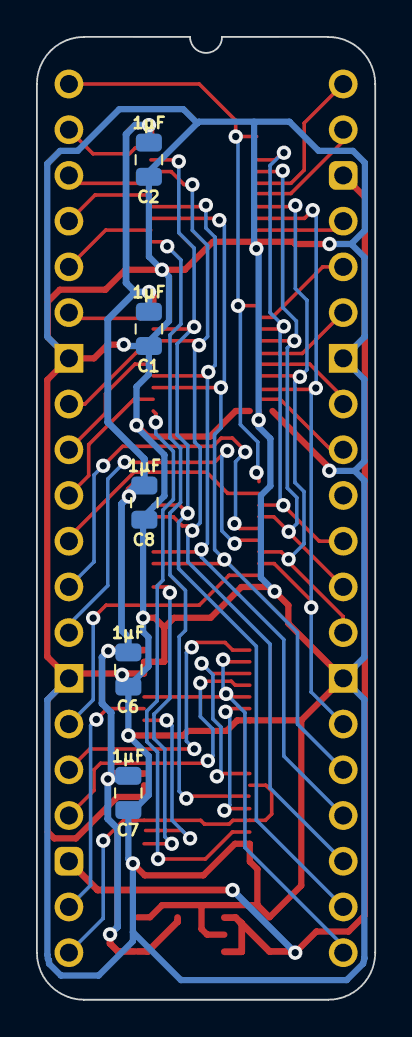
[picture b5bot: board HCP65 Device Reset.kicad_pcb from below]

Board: 2 copper layers, 18.8 x 53.5 mm, 16 parts (7 on the bottom side), 42 nets.

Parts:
C1, C2, C6, C7, C8: 1μF; C_0805
C9, C10: 10μF; C_0805
IC2, IC6, IC9: 74LVC273PW,118; SOP65P640X110-20N
IC7: 74LVC02APW,118; SOP65P640X110-14N
IC8: 74LVC08APW,112; SOP65P640X110-14N
IC11: AP7365-33WG-7; SOT95P285X130-5N
J1, J3: Pin_Header_01x20; PinHeader_1x20_P2.54mm_Vertical
J4: Conn_02x20_Counter_Clockwise; DIP-40_Board_W15.24mm

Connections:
5V: C9.1, IC11.1 (6VIn), IC11.3 (EN), J4.3, J4.23
/3.3V: C1.1, C2.1, C6.1, C7.1, C8.1, C10.1, IC2.20 (3V), IC6.20 (3V), IC7.14 (3V), IC8.14 (3V), IC9.20 (3V), IC11.5 (3.3VOut)
/Write Device Reset_{ 1..7}: IC7.3 (1Y), IC8.1 (1A)
/Write Device Reset_{ 1..7}·~CLK: IC2.11 (CP), IC8.3 (1Y)
/Write Device Reset_{ 8..15}: IC7.6 (2Y), IC8.4 (2A)
/Write Device Reset_{ 8..15}·~CLK: IC6.11 (CP), IC8.6 (2Y)
/Write Device Reset_{ 16..19}: IC7.8 (3Y), IC8.9 (3A)
/Write Device Reset_{ 16..19}·~CLK: IC8.8 (3Y), IC9.11 (CP)
D0: IC2.3 (D0), IC6.3 (D0), IC9.3 (D0), J4.11
D1: IC2.4 (D1), IC6.4 (D1), IC9.4 (D1), J4.12
D2: IC2.7 (D2), IC6.7 (D2), IC9.7 (D2), J4.13
D3: IC2.8 (D3), IC6.8 (D3), IC9.8 (D3), J4.15
D4: IC2.13 (D4), IC6.13 (D4), IC9.13 (D4), J4.16
D5: IC2.14 (D5), IC6.14 (D5), IC9.14 (D5), J4.17
D6: IC2.17 (D6), IC6.17 (D6), IC9.17 (D6), J4.18
D7: IC2.18 (D7), IC6.18 (D7), IC9.18 (D7), J4.19
GND: C1.2, C2.2, C6.2, C7.2, C8.2, C9.2, C10.2, IC2.10 (GND), IC6.10 (GND), IC7.7 (GND), IC7.12 (4A), IC7.13 (4B), IC8.7 (GND), IC8.12 (4A), IC8.13 (4B), IC9.10 (GND), IC11.2 (GND), J4.7, J4.14, J4.27, J4.34
~CLK: IC8.2 (1B), IC8.5 (2B), IC8.10 (3B), J4.21
~Device Enable_{ 1..7}: IC7.1 (1A), J4.25
~Device Enable_{ 8..15}: IC7.4 (2A), J4.24
~Device Enable_{ 16..19}: IC7.9 (3A), J4.22
~Reset: IC2.1 (~MR), IC6.1 (~MR), IC9.1 (~MR), J4.40
~Reset_{Device}1: IC2.5 (Q1), J4.1
~Reset_{Device}2: IC2.6 (Q2), J4.2
~Reset_{Device}3: IC2.9 (Q3), J4.4
~Reset_{Device}4: IC2.12 (Q4), J4.36
~Reset_{Device}5: IC2.15 (Q5), J4.37
~Reset_{Device}6: IC2.16 (Q6), J4.38
~Reset_{Device}7: IC2.19 (Q7), J4.39
~Reset_{Device}8: IC6.2 (Q0), J4.5
~Reset_{Device}9: IC6.5 (Q1), J4.6
~Reset_{Device}10: IC6.6 (Q2), J4.8
~Reset_{Device}11: IC6.9 (Q3), J4.9
~Reset_{Device}12: IC6.12 (Q4), J4.31
~Reset_{Device}13: IC6.15 (Q5), J4.32
~Reset_{Device}14: IC6.16 (Q6), J4.33
~Reset_{Device}15: IC6.19 (Q7), J4.35
~Reset_{Device}16: IC9.2 (Q0), J4.30
~Reset_{Device}17: IC9.5 (Q1), J4.29
~Reset_{Device}18: IC9.6 (Q2), J4.28
~Reset_{Device}19: IC9.9 (Q3), J4.26
~WD: IC7.2 (1B), IC7.5 (2B), IC7.10 (3B), J4.20
